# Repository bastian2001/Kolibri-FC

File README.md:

# RP2350 Flight Controller for FPV

I wanted to have some fun designing my own flight controller in both hardware and software. [This project of mine](https://github.com/bastian2001/Hardware-DShot-on-RP2040) ([superseded](https://github.com/bastian2001/pico-bidir-dshot/)) served as a proof of concept (and mostly minimal example) that the RP2040 is capable of driving DShot through the PIO (Programmable IO) hardware.

Main software features:

- Configurator
- Acro and angle modes
- altitude and position hold modes (working, but need to be tuned)
- ELRS
- GPS (UBlox) and Compass (HMC5883 + QMC5883L)
- Bidirectional DShot 4800 (tested up to 1200)
- Variable frequency beeper with WAV support
- SD-Blackbox incl. viewer
- Barometer (Goertek SPL06-001 + STM LPS22HB)

> [!NOTE]
> The PCB now lives in [its own repo](https://github.com/bastian2001/Kolibri-FC-Hardware)

Future shit:

- return to home and waypoint mission (incl. emergency switch)
- 3D camera dolly
- trick trainer, that does a trick for you and displays in the OSD how good or bad you were at repeating that trick

Practically speaking, is there any reason to choose this over Betaflight or iNav? Likely not, but I want to have a challenge.

## Configurator screenshots

Home Page with a general preview of the quad's orientation, some status info and general controls

The Hardware Setup Page allows you to tell the FC how you wired up everything, and how everything is attached together mechanically. You can create UARTs as much as the resources allow for it, normal or PIO based. It is all in one spot so you can quickly check whether all devices are recognized.

Blackbox viewer integrated into the configurator. You can record ELRS data, gyro rates, PID, a bunch of sensor data and much more. Size is practically unlimited (SD card logging), for me it is usually in the range of 80-150KB/s. Integrated filtering to smooth noisy data, multiple graphs and multiple traces per graph, JSON converter for external analysis, pinch to zoom (touchscreen support).

Tasks viewer shows the execution duration and frequency of all the tasks to check they're running fast enough and to aid optimization of code. Some functions are not always running, hence the NaN and 0Hz.

Receiver Page shows status of the RX and each channel. It also allows you to set which switch is used for arming etc., and you can set things up on the receiver, transmitter and other devices (ELRS 4.0+ required (maybe Crossfire also works)).

Tuning of PIDs and filters, as well as rates, with live preview of rates and Blender-style input boxes

GPS + Mag page shows X/Y Y/Z and Z/X graphs of the magnetometer to check calibration and skew. Lower side shows data obtained by the GPS (no GPS fix right now, so time is off)

CLI for some additional settings and easier development and testing of new ones

More features: Motor remapping and Analog VTX channel adjustment (IRC Tramp)

You can also connect via you ELRS' WiFi, and everything except very large CLI operations and the Tasks viewer works the same way (512 byte limit on ELRS side). Even blackbox data can be transmitted over WiFi.

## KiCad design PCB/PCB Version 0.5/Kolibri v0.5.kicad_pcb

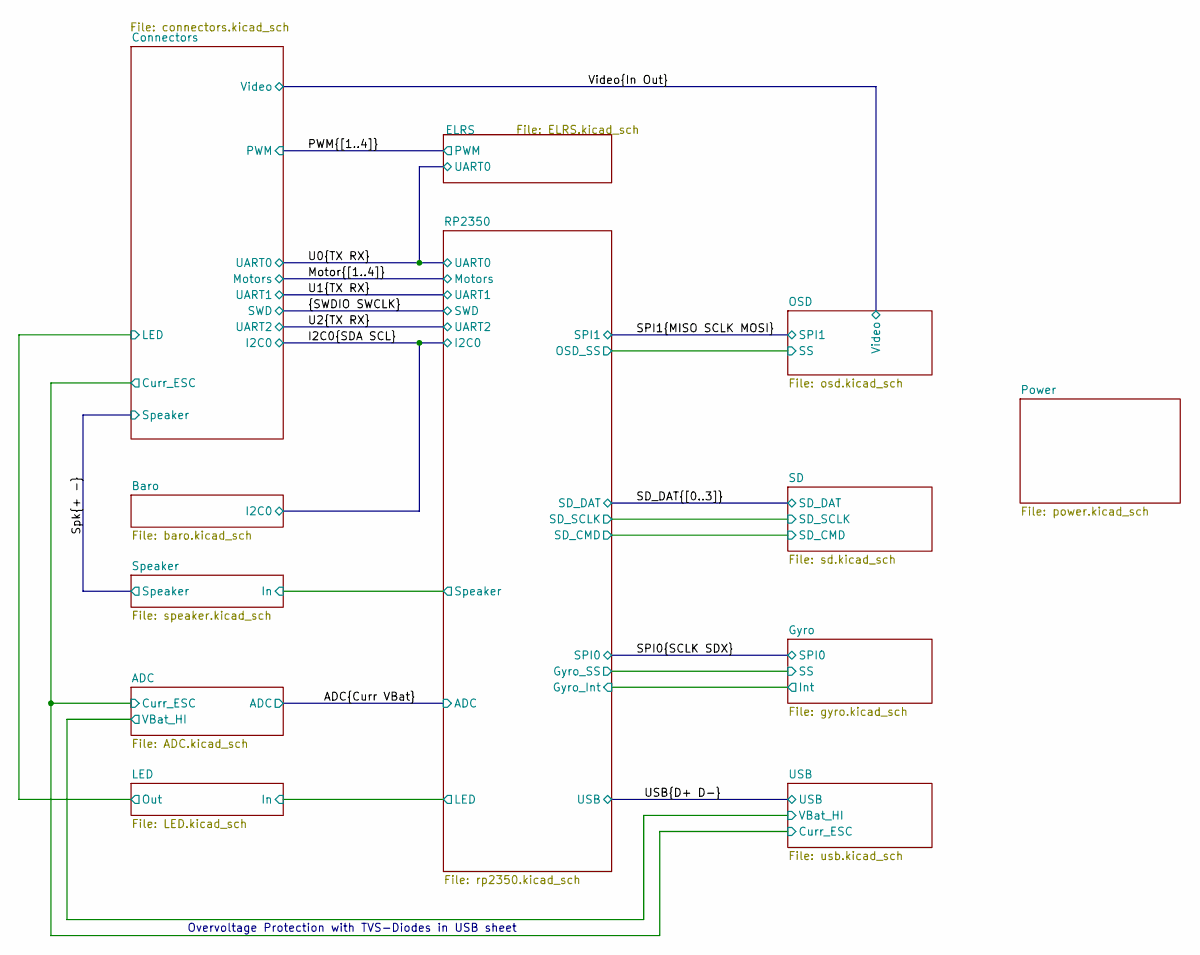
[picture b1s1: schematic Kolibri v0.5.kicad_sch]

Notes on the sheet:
Overvoltage Protection with TVS-Diodes in USB sheet

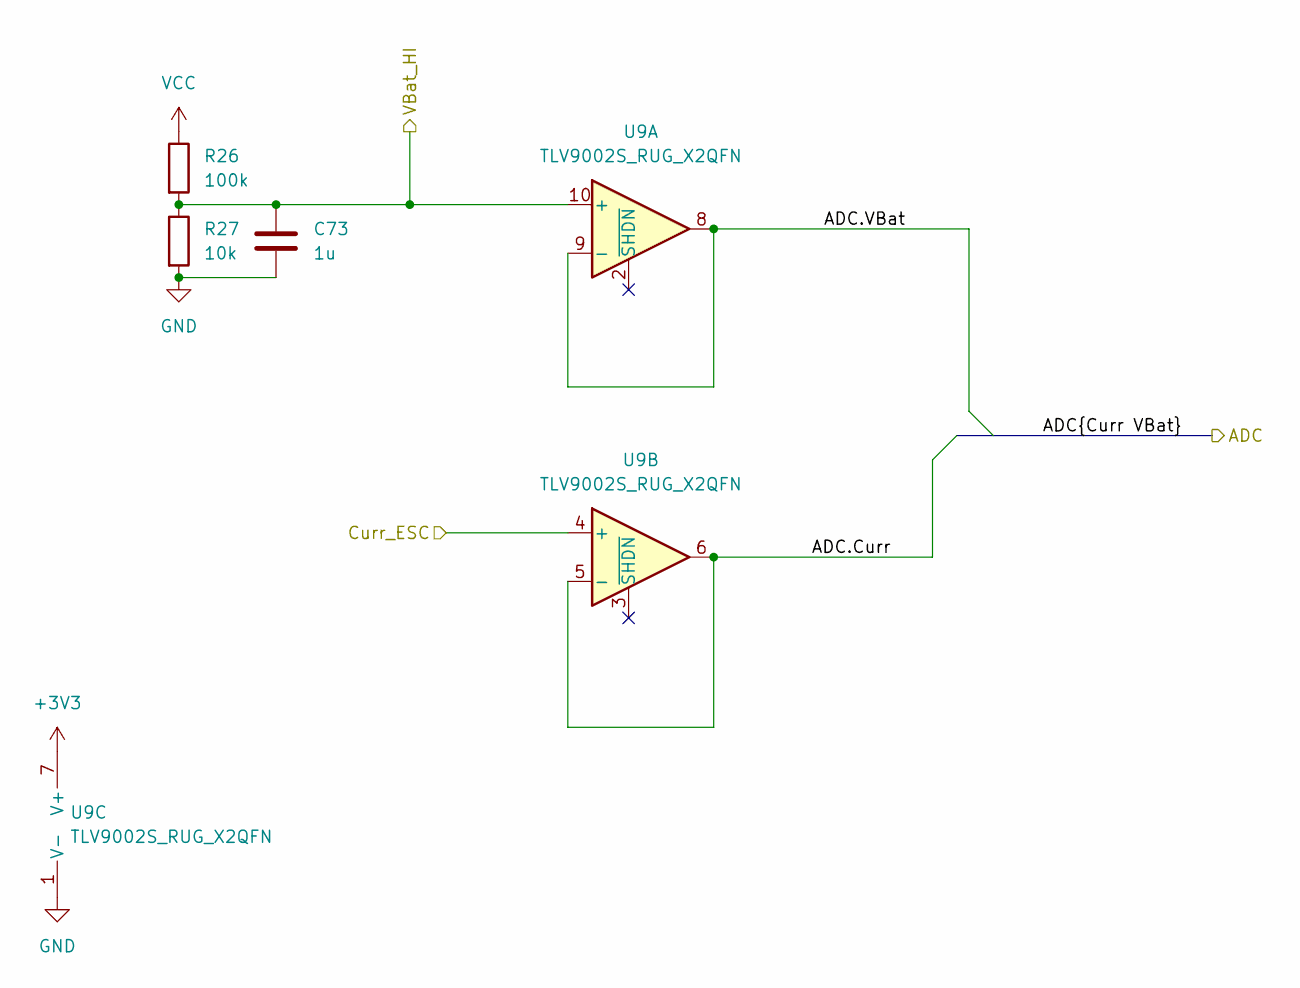
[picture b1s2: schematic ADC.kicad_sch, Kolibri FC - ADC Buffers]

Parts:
C73: 1u; C_0402_1005Metric
R26: 100k; R_0402_1005Metric
R27: 10k; R_0402_1005Metric
U9: TLV9002S_RUG_X2QFN; Texas_X2QFN_RUG_10pin_1.5x2mm

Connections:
+3V3: U9.7 (V+); also elsewhere on the board
/ADC.Curr: U9.5 (-), U9.6; also elsewhere on the board
/ADC.VBat: U9.8, U9.9 (-); also elsewhere on the board
/ADC/VBat_HI: C73.2, R26.2, R27.1, U9.10 (+); also elsewhere on the board
/Connectors/Curr_ESC: U9.4 (+); also elsewhere on the board
GND: C73.1, R27.2, U9.1 (V-); also elsewhere on the board

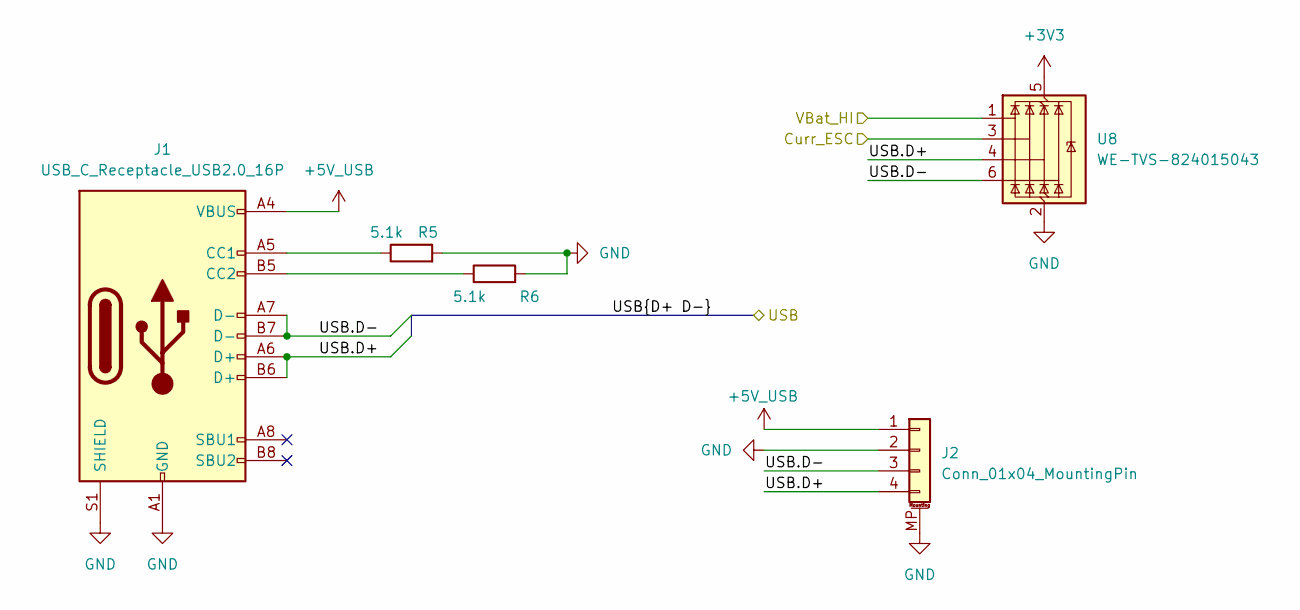
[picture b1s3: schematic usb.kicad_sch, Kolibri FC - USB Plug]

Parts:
J1: USB_C_Receptacle_USB2.0_16P; USB-C SMD+THT
J2: Conn_01x04_MountingPin; JST_SH_SM04B-SRSS-TB_1x04-1MP_P1.00mm_Horizontal
R5, R6: 5.1k; R_0402_1005Metric
U8: WE-TVS-824015043; SOT-23-6

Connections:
+3V3: U8.5 (VBUS); also elsewhere on the board
+5V_USB: J1.A4 (VBUS), J1.A9 (VBUS), J1.B4 (VBUS), J1.B9 (VBUS), J2.1; also elsewhere on the board
/ADC/VBat_HI: U8.1 (I/O1); also elsewhere on the board
/Connectors/Curr_ESC: U8.3 (I/O2); also elsewhere on the board
GND: J1.A1 (GND), J1.A12 (GND), J1.B1 (GND), J1.B12 (GND), J1.S1 (SHIELD), J2.2, J2.MP (MountPin), R5.2, R6.2, U8.2 (GND); also elsewhere on the board
unnamed: J1.A5 (CC1), R5.1
unnamed: J1.B5 (CC2), R6.1

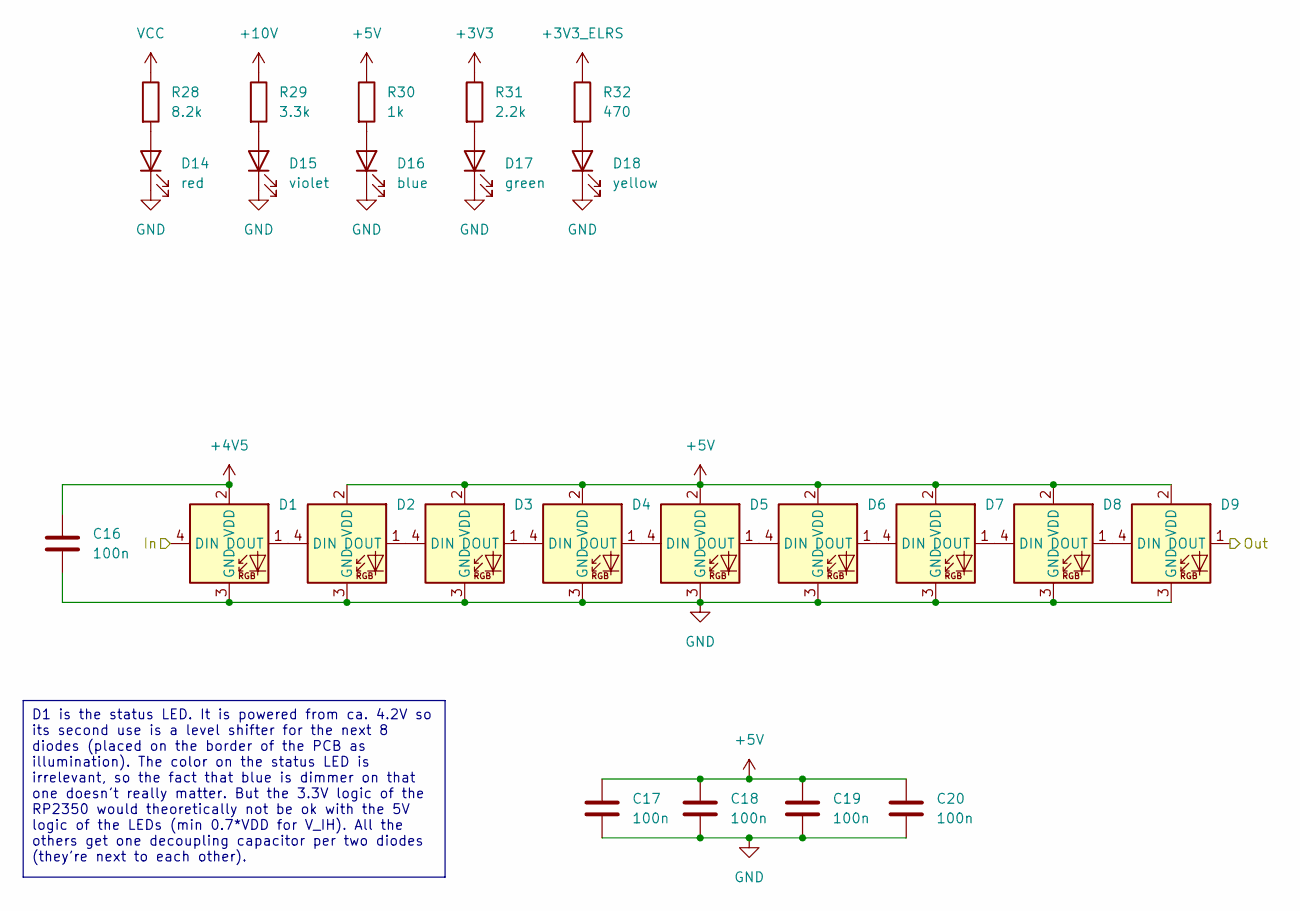
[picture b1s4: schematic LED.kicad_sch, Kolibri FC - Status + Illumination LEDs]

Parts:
C16, C17, C18, C19, C20: 100n; C_0402_1005Metric
D1, D2, D3, D4, D5, D6, D7, D8, D9: WS2812B_1615
D14: red; LED_0603_1608Metric
D15: violet; LED_0603_1608Metric
D16: blue; LED_0603_1608Metric
D17: green; LED_0603_1608Metric
D18: yellow; LED_0603_1608Metric
R28: 8.2k; R_0402_1005Metric_Pad0.72x0.64mm_HandSolder
R29: 3.3k; R_0402_1005Metric_Pad0.72x0.64mm_HandSolder
R30: 1k; R_0402_1005Metric_Pad0.72x0.64mm_HandSolder
R31: 2.2k; R_0402_1005Metric_Pad0.72x0.64mm_HandSolder
R32: 470; R_0402_1005Metric_Pad0.72x0.64mm_HandSolder

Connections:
+3V3: R31.1; also elsewhere on the board
+3V3_ELRS: R32.1; also elsewhere on the board
+4V5: C16.1, D1.2 (VDD); also elsewhere on the board
+5V: C17.1, C18.1, C19.1, C20.1, D2.2 (VDD), D3.2 (VDD), D4.2 (VDD), D5.2 (VDD), D6.2 (VDD), D7.2 (VDD), D8.2 (VDD), D9.2 (VDD), R30.1; also elsewhere on the board
/Connectors/LED: D9.1 (DOUT); also elsewhere on the board
/RP2350/LED: D1.4 (DIN); also elsewhere on the board
GND: C16.2, C17.2, C18.2, C19.2, C20.2, D1.3 (GND), D2.3 (GND), D3.3 (GND), D4.3 (GND), D5.3 (GND), D6.3 (GND), D7.3 (GND), D8.3 (GND), D9.3 (GND), D14.1 (K), D15.1 (K), D16.1 (K), D17.1 (K), D18.1 (K); also elsewhere on the board
unnamed: D1.1 (DOUT), D2.4 (DIN)
unnamed: D2.1 (DOUT), D3.4 (DIN)
unnamed: D3.1 (DOUT), D4.4 (DIN)
unnamed: D4.1 (DOUT), D5.4 (DIN)
unnamed: D5.1 (DOUT), D6.4 (DIN)
unnamed: D6.1 (DOUT), D7.4 (DIN)
unnamed: D7.1 (DOUT), D8.4 (DIN)
unnamed: D8.1 (DOUT), D9.4 (DIN)
unnamed: D14.2 (A), R28.2
unnamed: D15.2 (A), R29.2
unnamed: D16.2 (A), R30.2
unnamed: D17.2 (A), R31.2
unnamed: D18.2 (A), R32.2

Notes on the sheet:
D1 is the status LED. It is powered from ca. 4.2V so its second use is a level shifter for the next 8 diodes (placed on the border of the PCB as illumination). The color on the status LED is irrelevant, so the fact that blue is dimmer on that one doesn't really matter. But the 3.3V logic of the RP2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

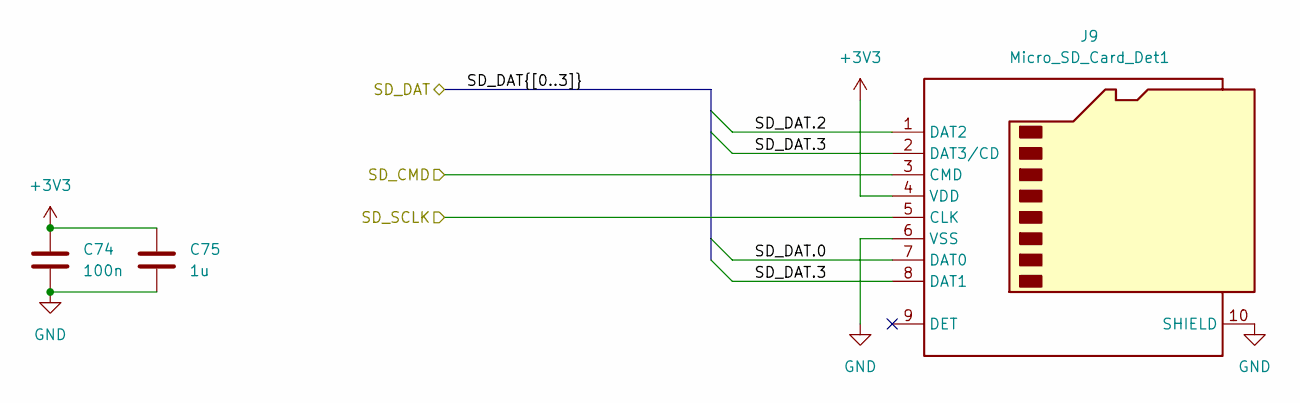
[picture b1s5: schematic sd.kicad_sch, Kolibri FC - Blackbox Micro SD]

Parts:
C74: 100n; C_0402_1005Metric_Pad0.74x0.62mm_HandSolder
C75: 1u; C_0402_1005Metric_Pad0.74x0.62mm_HandSolder
J9: Micro_SD_Card_Det1; Micro SD Card (TF)

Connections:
+3V3: C74.1, C75.1, J9.4 (VDD); also elsewhere on the board
/RP2350/SD_CMD: J9.3 (CMD); also elsewhere on the board
/RP2350/SD_SCLK: J9.5 (CLK); also elsewhere on the board
/SD_DAT.0: J9.7 (DAT0); also elsewhere on the board
/SD_DAT.2: J9.1 (DAT2); also elsewhere on the board
GND: C74.2, C75.2, J9.6 (VSS), J9.10 (SHIELD); also elsewhere on the board

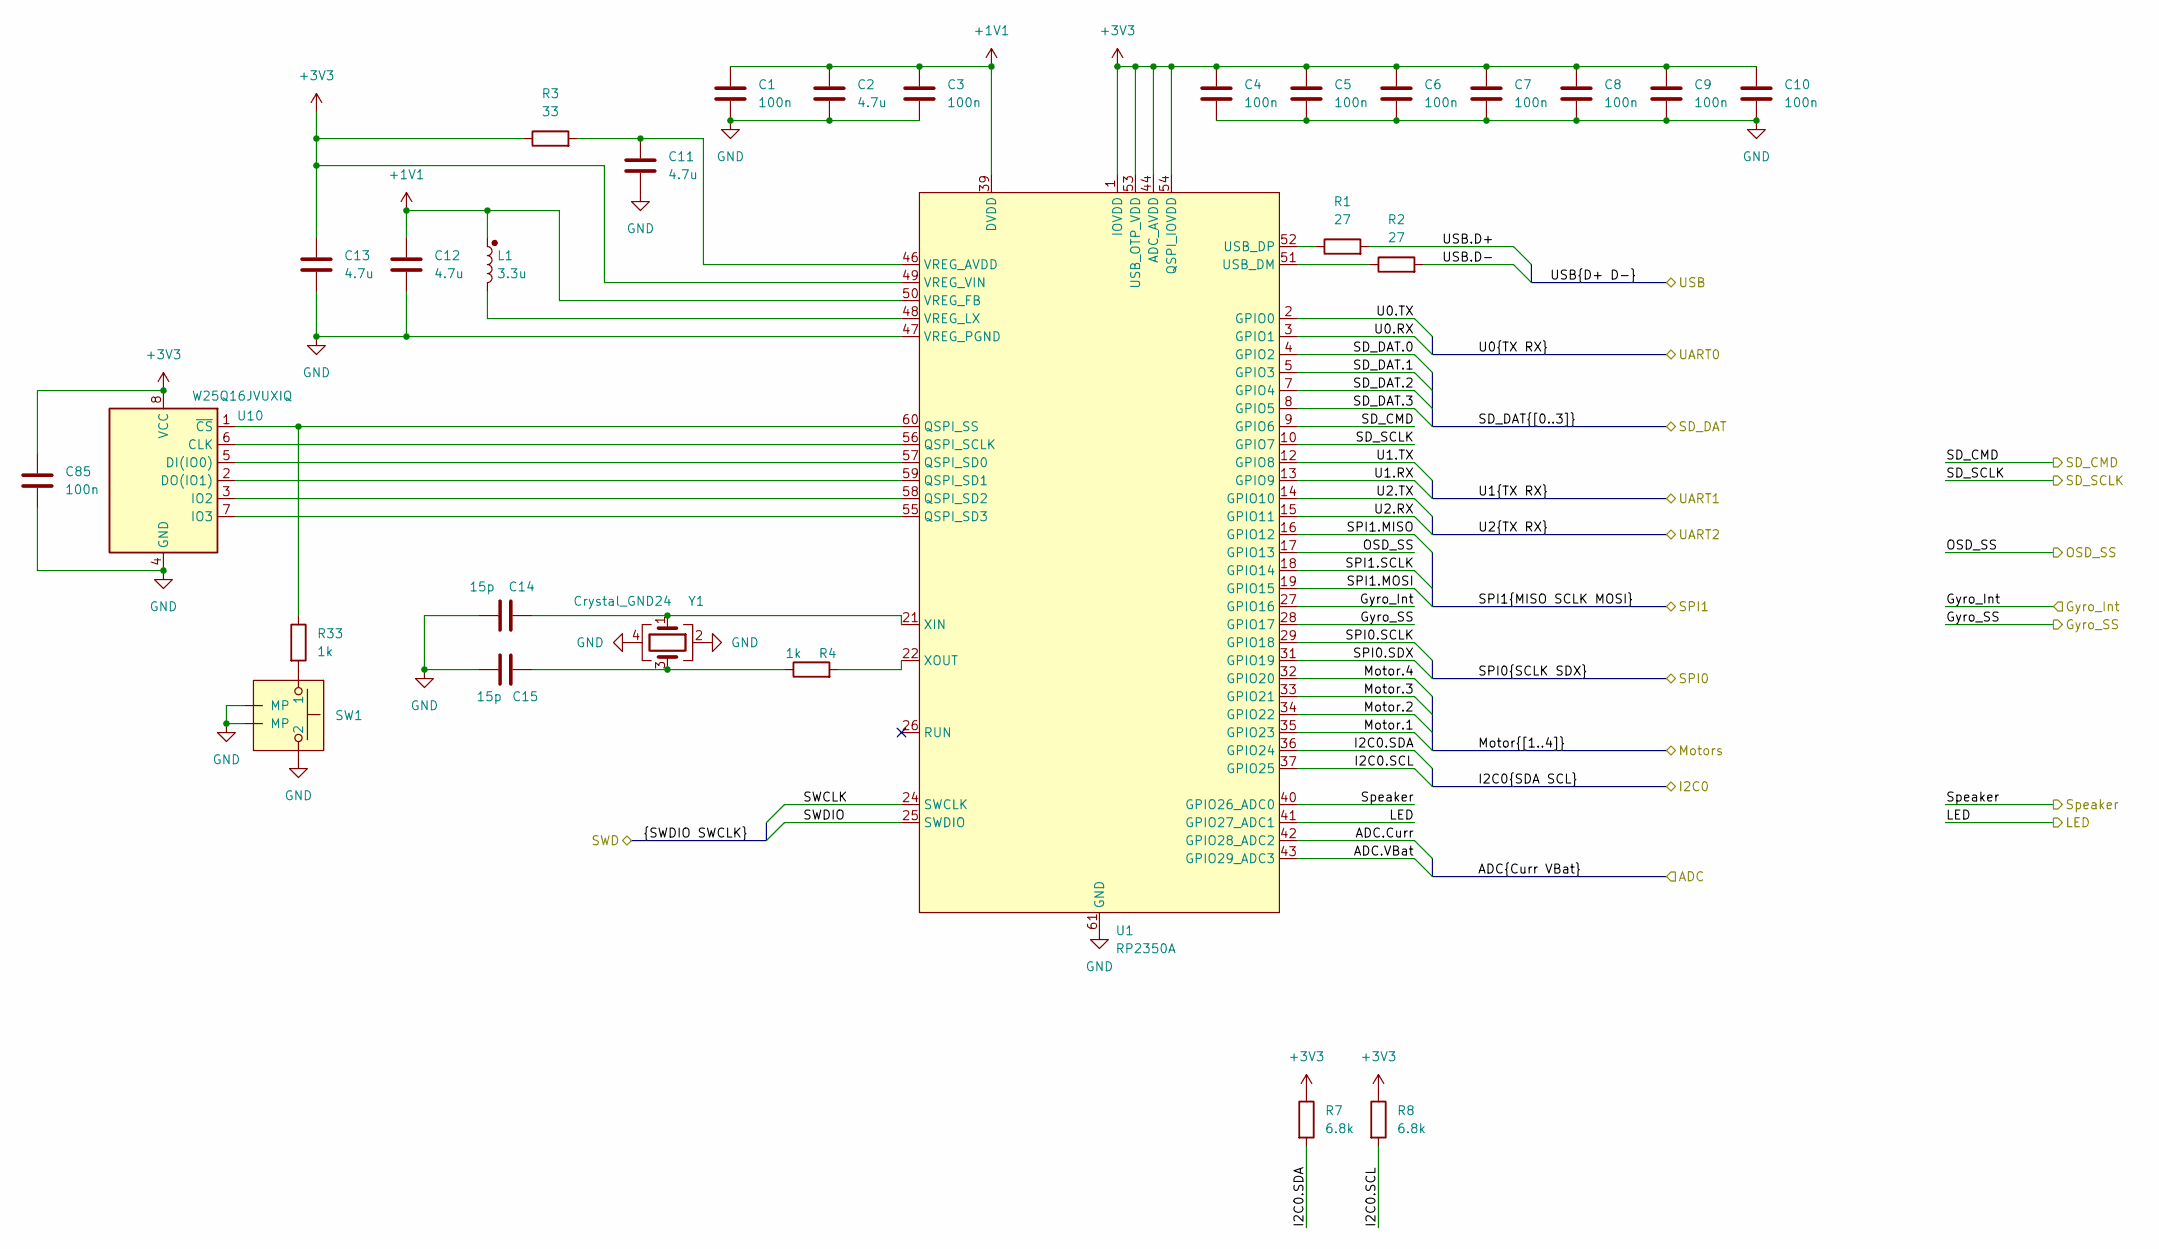
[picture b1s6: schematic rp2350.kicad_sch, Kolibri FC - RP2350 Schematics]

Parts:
C1, C3, C4, C5, C6, C7, C8, C9, C10: 100n; C_0402_1005Metric_Pad0.74x0.62mm_HandSolder
C2: 4.7u; C_0402_1005Metric_Pad0.74x0.62mm_HandSolder
C11, C12, C13: 4.7u; C_0402_1005Metric
C14, C15: 15p; C_0402_1005Metric_Pad0.74x0.62mm_HandSolder
C85: 100n; C_0402_1005Metric
L1: 3.3u; Abracon AOTA 0806
R1, R2: 27; R_0402_1005Metric
R3: 33; R_0402_1005Metric
R4, R33: 1k; R_0402_1005Metric_Pad0.72x0.64mm_HandSolder
R7, R8: 6.8k; R_0402_1005Metric_Pad0.72x0.64mm_HandSolder
SW1: Button C530669 wo holes
U1: RP2350A; QFN-60_EP_7x7_Pitch0.4mm
U10: W25Q16JVUXIQ; Winbond_USON-8-1EP_3x2mm_P0.5mm_EP0.2x1.6mm
Y1: Crystal_GND24; Crystal_SMD_3225-4Pin_3.2x2.5mm

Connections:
+1V1: C1.1, C2.1, C3.1, C12.1, L1.1, U1.6 (DVDD), U1.23 (DVDD), U1.39 (DVDD), U1.50 (VREG_FB)
+3V3: C4.1, C5.1, C6.1, C7.1, C8.1, C9.1, C10.1, C13.1, C85.1, R3.1, R7.1, R8.1, U1.1 (IOVDD), U1.11 (IOVDD), U1.20 (IOVDD), U1.30 (IOVDD), U1.38 (IOVDD), U1.44 (ADC_AVDD), U1.45 (IOVDD), U1.49 (VREG_VIN), U1.53 (USB_OTP_VDD), U1.54 (QSPI_IOVDD), U10.8 (VCC); also elsewhere on the board
/ADC.Curr: U1.42 (GPIO28_ADC2); also elsewhere on the board
/ADC.VBat: U1.43 (GPIO29_ADC3); also elsewhere on the board
/I2C0.SCL: R8.2, U1.37 (GPIO25); also elsewhere on the board
/I2C0.SDA: R7.2, U1.36 (GPIO24); also elsewhere on the board
/Motor.1: U1.35 (GPIO23); also elsewhere on the board
/Motor.2: U1.34 (GPIO22); also elsewhere on the board
/Motor.3: U1.33 (GPIO21); also elsewhere on the board
/Motor.4: U1.32 (GPIO20); also elsewhere on the board
/RP2350/Gyro_Int: U1.27 (GPIO16); also elsewhere on the board
/RP2350/Gyro_SS: U1.28 (GPIO17); also elsewhere on the board
/RP2350/LED: U1.41 (GPIO27_ADC1); also elsewhere on the board
/RP2350/OSD_SS: U1.17 (GPIO13); also elsewhere on the board
/RP2350/SD_CMD: U1.9 (GPIO6); also elsewhere on the board
/RP2350/SD_SCLK: U1.10 (GPIO7); also elsewhere on the board
/RP2350/Speaker: U1.40 (GPIO26_ADC0); also elsewhere on the board
/SD_DAT.0: U1.4 (GPIO2); also elsewhere on the board
/SD_DAT.2: U1.7 (GPIO4); also elsewhere on the board
/SPI0.SCLK: U1.29 (GPIO18); also elsewhere on the board
/SPI0.SDX: U1.31 (GPIO19); also elsewhere on the board
/SPI1.MISO: U1.16 (GPIO12); also elsewhere on the board
/SPI1.MOSI: U1.19 (GPIO15); also elsewhere on the board
/SPI1.SCLK: U1.18 (GPIO14); also elsewhere on the board
/SWCLK: U1.24 (SWCLK); also elsewhere on the board
/SWDIO: U1.25 (SWDIO); also elsewhere on the board
/U0.RX: U1.3 (GPIO1); also elsewhere on the board
/U0.TX: U1.2 (GPIO0); also elsewhere on the board
/U2.RX: U1.15 (GPIO11); also elsewhere on the board
/U2.TX: U1.14 (GPIO10); also elsewhere on the board
GND: C1.2, C2.2, C3.2, C4.2, C5.2, C6.2, C7.2, C8.2, C9.2, C10.2, C11.2, C12.2, C13.2, C14.1, C15.1, C85.2, SW1.2, SW1.3 (MP), SW1.4 (MP), U1.47 (VREG_PGND), U1.61 (GND), U10.4 (GND), U10.9 (EP), Y1.2, Y1.4; also elsewhere on the board
unnamed: C15.2, R4.1, Y1.3
unnamed: R33.2, SW1.1
unnamed: U1.56 (QSPI_SCLK), U10.6 (CLK)
unnamed: U1.57 (QSPI_SD0), U10.5 (DI(IO0))
unnamed: U1.59 (QSPI_SD1), U10.2 (DO(IO1))
unnamed: U1.58 (QSPI_SD2), U10.3 (IO2)
unnamed: U1.55 (QSPI_SD3), U10.7 (IO3)
unnamed: R33.1, U1.60 (QSPI_SS), U10.1 (~CS)
unnamed: R2.1, U1.51 (USB_DM)
unnamed: R1.1, U1.52 (USB_DP)
unnamed: C11.1, R3.2, U1.46 (VREG_AVDD)
unnamed: L1.2, U1.48 (VREG_LX)
unnamed: C14.2, U1.21 (XIN), Y1.1
unnamed: R4.2, U1.22 (XOUT)

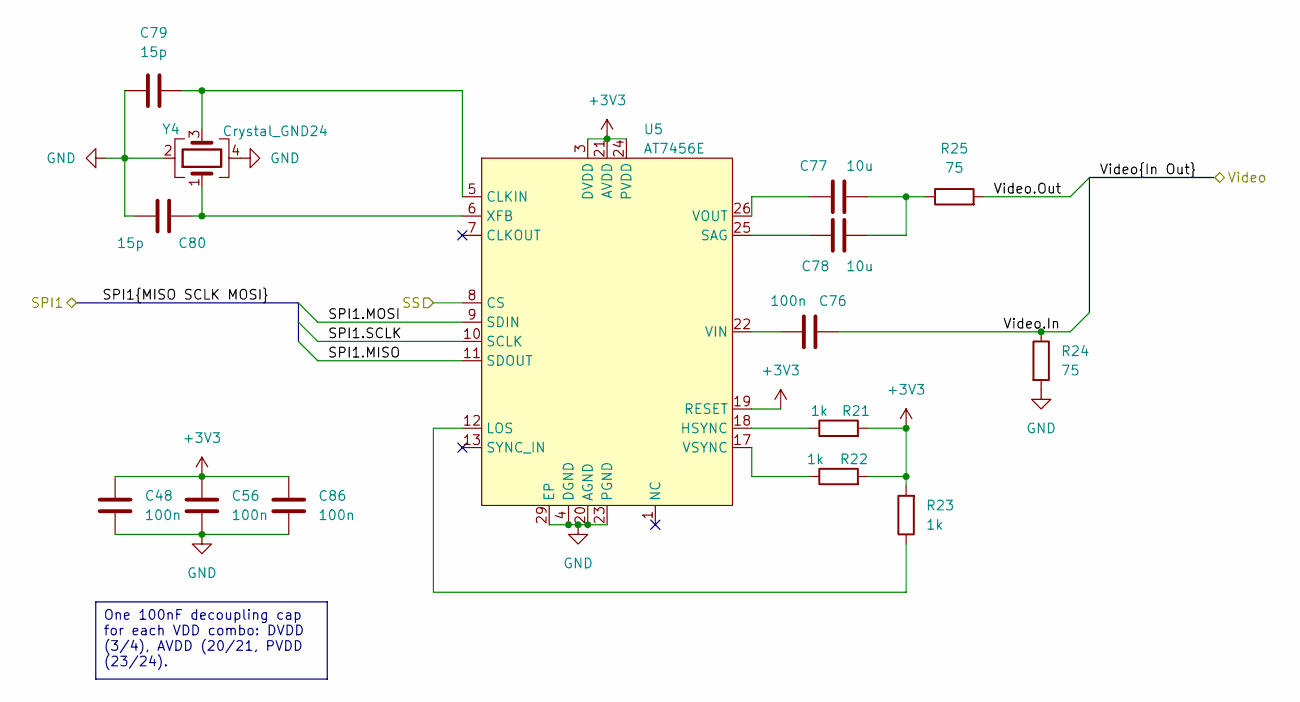
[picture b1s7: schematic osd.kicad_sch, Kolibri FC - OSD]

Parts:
C48, C76: 100n; C_0402_1005Metric
C56, C86: 100n; C_0402_1005Metric_Pad0.74x0.62mm_HandSolder
C77, C78: 10u; C_0402_1005Metric_Pad0.74x0.62mm_HandSolder
C79, C80: 15p; C_0402_1005Metric
R21, R22, R23: 1k; R_0402_1005Metric
R24: 75; R_0402_1005Metric
R25: 75; R_0402_1005Metric_Pad0.72x0.64mm_HandSolder
U5: AT7456E; HTSSOP-28-1EP_4.4x9.7mm_P0.65mm_EP2.75x6.2mm
Y4: Crystal_GND24; Crystal_SMD_3225-4Pin_3.2x2.5mm

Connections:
+3V3: C48.1, C56.1, C86.1, R21.2, R22.2, R23.2, U5.3 (DVDD), U5.19 (RESET), U5.21 (AVDD), U5.24 (PVDD); also elsewhere on the board
/RP2350/OSD_SS: U5.8 (CS); also elsewhere on the board
/SPI1.MISO: U5.11 (SDOUT); also elsewhere on the board
/SPI1.MOSI: U5.9 (SDIN); also elsewhere on the board
/SPI1.SCLK: U5.10 (SCLK); also elsewhere on the board
/Video.In: C76.2, R24.1; also elsewhere on the board
/Video.Out: R25.2; also elsewhere on the board
GND: C48.2, C56.2, C79.1, C80.2, C86.2, R24.2, U5.4 (DGND), U5.20 (AGND), U5.23 (PGND), U5.29 (EP), Y4.2, Y4.4; also elsewhere on the board
unnamed: C77.2, C78.1, R25.1
unnamed: C79.2, U5.5 (CLKIN), Y4.3
unnamed: R21.1, U5.18 (HSYNC)
unnamed: R23.1, U5.12 (LOS)
unnamed: C78.2, U5.25 (SAG)
unnamed: C76.1, U5.22 (VIN)
unnamed: R22.1, U5.17 (VSYNC)
unnamed: C80.1, U5.6 (XFB), Y4.1

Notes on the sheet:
One 100nF decoupling cap for each VDD combo: DVDD (3/4), AVDD (20/21, PVDD (23/24).

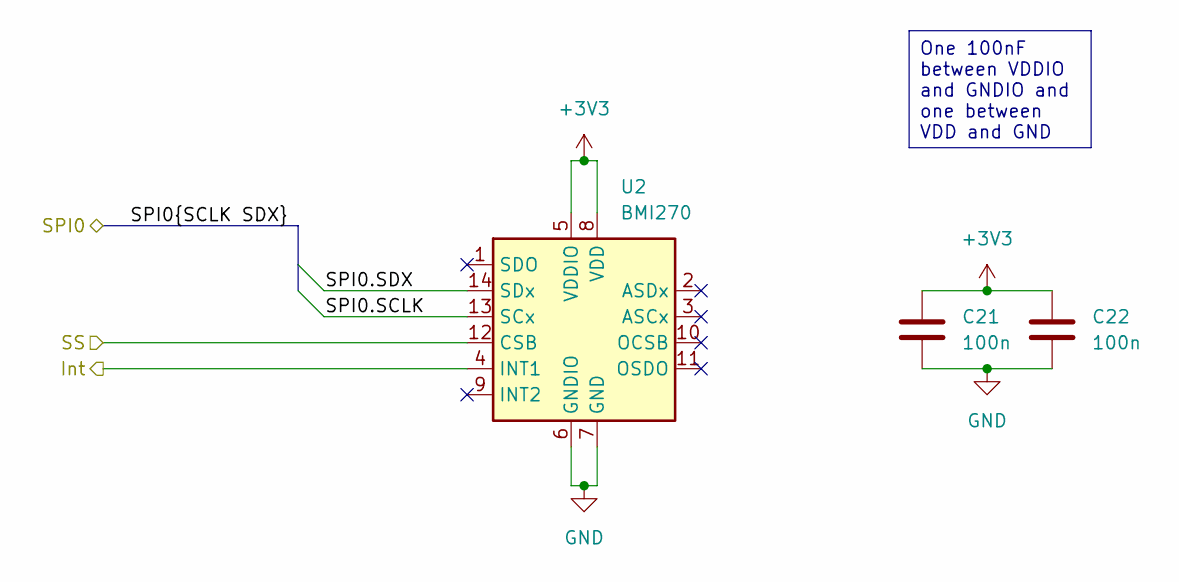
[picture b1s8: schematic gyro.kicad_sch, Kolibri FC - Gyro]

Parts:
C21, C22: 100n; C_0402_1005Metric
U2: BMI270; Bosch_LGA-14_3x2.5mm_P0.5mm

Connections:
+3V3: C21.1, C22.1, U2.5 (VDDIO), U2.8 (VDD); also elsewhere on the board
/RP2350/Gyro_Int: U2.4 (INT1); also elsewhere on the board
/RP2350/Gyro_SS: U2.12 (CSB); also elsewhere on the board
/SPI0.SCLK: U2.13 (SCx); also elsewhere on the board
/SPI0.SDX: U2.14 (SDx); also elsewhere on the board
GND: C21.2, C22.2, U2.6 (GNDIO), U2.7 (GND); also elsewhere on the board

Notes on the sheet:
One 100nF between VDDIO and GNDIO and one between VDD and GND

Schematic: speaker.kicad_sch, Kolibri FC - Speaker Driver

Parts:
D12: 1N4148WS; D_SOD-323
JP1: SolderJumper_3_Open; SolderJumper-3_P1.3mm_Open_RoundedPad1.0x1.5mm
Q1: BSS138; SOT-23

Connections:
/RP2350/Speaker: Q1.1 (G); also elsewhere on the board
/Spk.+: D12.1 (K), JP1.2 (C); also elsewhere on the board
/Spk.-: D12.2 (A), Q1.3 (D); also elsewhere on the board
GND: Q1.2 (S); also elsewhere on the board

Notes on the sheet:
PWM Speaker driver
Q1 acts as a pulldown, D12 is the flyback. Q1's gate is PWMed at 44.1kHz. By adjusting the duty cycle of the PWM, we can either pull Spk.- lower (higher duty cycle) or higher (lower duty cycle), to write our sound samples to Spk.-. This way, we get a DAC without proper DAC hardware. Alternatively, 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

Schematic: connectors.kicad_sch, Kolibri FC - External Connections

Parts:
J5: Conn_01x08_MountingPin; JST_SH_SM08B-SRSS-TB_1x08-1MP_P1.00mm_Horizontal
J6, J7: Conn_01x06_MountingPin; JST_SH_SM06B-SRSS-TB_1x06-1MP_P1.00mm_Horizontal
J8: Conn_01x03_MountingPin; JST_SH_SM03B-SRSS-TB_1x03-1MP_P1.00mm_Horizontal
P1, P2, P3, P4, P5, P6, P7, P8, P9, P10, P11, P12, P13, P14, P15, P16, P17: Solder_Pad_rounded
P18, P19, P20, P21, P22: Solder_Pad_rounded_dual
P23, P24, P25: Solder_Pad_rect_dual
P26, P27: Solder_Pad_rect
P28, P29, P30, P33, P34: Solder_Pad_octa_dual
P31, P32: Solder_Pad_octa

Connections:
+3V3: P34.1, P34.2; also elsewhere on the board
+5V: J6.4, P29.1, P29.2, P30.1, P30.2, P31.1, P32.1; also elsewhere on the board
/Connectors/Curr_ESC: J5.8, P5.1; also elsewhere on the board
/Connectors/LED: P20.1, P20.2; also elsewhere on the board
/I2C0.SCL: J6.6, P9.1; also elsewhere on the board
/I2C0.SDA: J6.5, P8.1; also elsewhere on the board
/Motor.1: J5.3, P1.1; also elsewhere on the board
/Motor.2: J5.4, P2.1; also elsewhere on the board
/Motor.3: J5.5, P3.1; also elsewhere on the board
/Motor.4: J5.6, P4.1; also elsewhere on the board
/PWM.1: P12.1; also elsewhere on the board
/PWM.2: P13.1; also elsewhere on the board
/PWM.3: P14.1; also elsewhere on the board
/PWM.4: P15.1; also elsewhere on the board
/SWCLK: J8.1; also elsewhere on the board
/SWDIO: J8.3; also elsewhere on the board
/Spk.+: P21.1, P21.2; also elsewhere on the board
/Spk.-: P22.1, P22.2; also elsewhere on the board
/U0.RX: P17.1; also elsewhere on the board
/U0.TX: P16.1; also elsewhere on the board
/U2.RX: J7.4, P11.1; also elsewhere on the board
/U2.TX: J7.3, P10.1; also elsewhere on the board
/Video.In: P18.1, P18.2; also elsewhere on the board
/Video.Out: P19.1, P19.2; also elsewhere on the board
GND: J5.1, J5.MP (MountPin), J6.3, J6.MP (MountPin), J7.2, J7.5, J7.MP (MountPin), J8.2, J8.MP (MountPin), P23.1, P23.2, P24.1, P24.2, P25.1, P25.2, P26.1, P27.1; also elsewhere on the board

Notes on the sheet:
Power, GND
GPS
LED, Speaker
SWD
Analog Video
ESC
uses Mamba pinout
ELRS PWM outputs
Digital VTX
ELRS UART

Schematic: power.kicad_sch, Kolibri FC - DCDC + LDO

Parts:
C63, C64: 1u; C_0603_1608Metric
C65, C71: 100n; C_0402_1005Metric
C66: 47u; C_1206_3216Metric
C67, C70: 100n; C_0402_1005Metric_Pad0.74x0.62mm_HandSolder
C68, C69: 2.2u; C_1206_3216Metric
C72: 22u; C_0805_2012Metric
C81, C82, C83, C84: 1u; C_0402_1005Metric
D10, D13: 1N4148WS; D_SOD-323
IC5, IC6: LMR38025SDRRR; SON50P300X300X80-13N; Mouser Part Number 595-LMR38025SDRRR
L7, L8: 4.7u; L_Cenker_CKCS4020
R13: 100k; R_0402_1005Metric
R14: 39k; R_0402_1005Metric
R15: 40.2k; R_0402_1005Metric_Pad0.72x0.64mm_HandSolder
R16, R20: 10k; R_0402_1005Metric_Pad0.72x0.64mm_HandSolder
R17: 22.6k; R_0402_1005Metric
R18: 21.5k; R_0402_1005Metric
R19: 90.9k; R_0402_1005Metric_Pad0.72x0.64mm_HandSolder
U4: TPS2116DRL; SOT-583-8
U6: LP5912-3.3DRV; WSON-6-1EP_2x2mm_P0.65mm_EP1x1.6mm_ThermalVias
U7: TPS746-3.3DRV; WSON-6-1EP_2x2mm_P0.65mm_EP1x1.6mm_ThermalVias

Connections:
+3V3: C82.1, U6.1 (OUT); also elsewhere on the board
+3V3_ELRS: C84.1, U7.1 (OUT); also elsewhere on the board
+4V5: D10.1 (K); also elsewhere on the board
+5V: C63.2, C64.2, C81.1, C83.1, D10.2 (A), D13.1 (K), U4.2 (VOUT), U4.7 (VOUT), U6.4 (EN), U6.6 (IN), U7.4 (EN), U7.6 (IN); also elsewhere on the board
+5V_BUCK: C66.1, D13.2 (A), L7.2, R13.1, R15.1, U4.3 (VIN1), U4.5 (MODE)
+5V_USB: U4.6 (VIN2); also elsewhere on the board
GND: C63.1, C64.1, C66.2, C67.2, C68.2, C69.2, C70.2, C72.2, C81.2, C82.2, C83.2, C84.2, IC5.1 (GND_1), IC5.2 (GND_2), IC5.13 (EPAD), IC6.1 (GND_1), IC6.2 (GND_2), IC6.13 (EPAD), R14.2, R16.2, R17.2, R18.2, R20.2, U4.1 (GND), U6.3 (PG), U6.5 (GND), U6.7 (EP), U7.3 (GND), U7.5 (PG), U7.7 (EP); also elsewhere on the board
unnamed: C65.1, IC5.10 (BOOT)
unnamed: IC5.8 (FB), R15.2, R16.1
unnamed: IC5.7 (RT/SYNC), R17.1
unnamed: C65.2, IC5.11 (SW_1), IC5.12 (SW_2), L7.1
unnamed: C71.1, IC6.10 (BOOT)
unnamed: IC6.8 (FB), R19.2, R20.1
unnamed: IC6.7 (RT/SYNC), R18.1
unnamed: C71.2, IC6.11 (SW_1), IC6.12 (SW_2), L8.1
unnamed: R13.2, R14.1, U4.4 (PR1)

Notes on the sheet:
Two separate 3.3V-rails to satisfy ELRS's requirement of a separate 3.3V supply. Both LDOs have an almost identical pinout where only PG and GND are swapped, but because both allow PG to be grounded, these can be used interchangeably, once testing is complete (if ELRS is ok with only 500mA).
Switches up to 4A (TPS2117) from +5V_USB or +5V_BUCK to +5V. Prefers buck over USB, threshold voltage is about 3.5V. The threshold voltage is low to prevent accidental switchover to USB during peak consumption (worst case in flight). Emergency diode for if that happens during flight.
12-45V -> 10V 2.5A (6.8uH inductor recommended, but this works)
3.3V 1A LDO (ELRS)
Used for the first RGB LED in each strip, not broken out.
12-45V -> 5V 2.5A
3.3V 500mA LDO (main)
4.2V Supply
5V SMPS
5V Power MUX
10V SMPS

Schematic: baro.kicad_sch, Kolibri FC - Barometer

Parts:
C23, C24: 100n; C_0402_1005Metric_Pad0.74x0.62mm_HandSolder
U11: LPS22HB; ST_HLGA-10_2x2mm_P0.5mm_LayoutBorder3x2y

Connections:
+3V3: C23.1, C24.1, U11.1 (Vdd_IO), U11.5 (SA0), U11.6 (~CS), U11.10 (VDD); also elsewhere on the board
/I2C0.SCL: U11.2 (SCL); also elsewhere on the board
/I2C0.SDA: U11.4 (SDA); also elsewhere on the board
GND: C23.2, C24.2, U11.3 (GND), U11.8 (GND), U11.9 (GND); also elsewhere on the board

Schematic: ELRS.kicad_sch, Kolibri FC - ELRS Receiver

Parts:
C25, C26, C27, C28, C33, C34, C40, C44, C45, C60, C62: 100n; C_0402_1005Metric_Pad0.74x0.62mm_HandSolder
C29, C30, C35, C50, C53: 1u; C_0402_1005Metric_Pad0.74x0.62mm_HandSolder
C31, C42, C43, C47, C55: 10n; C_0402_1005Metric_Pad0.74x0.62mm_HandSolder
C32: 1.5p; C_0402_1005Metric
C36: 10u; C_0402_1005Metric_Pad0.74x0.62mm_HandSolder
C37: 1.5p; C_0402_1005Metric_Pad0.74x0.62mm_HandSolder
C38, C39: 15p; C_0402_1005Metric_Pad0.74x0.62mm_HandSolder
C41, C61: 470n; C_0402_1005Metric_Pad0.74x0.62mm_HandSolder
C46, C57: 47p; C_0402_1005Metric
C49: 220p; C_0402_1005Metric_Pad0.74x0.62mm_HandSolder
C51, C52, C58, C59: DNF; C_0402_1005Metric
C54: 220p; C_0402_1005Metric
D11: WS2812B_1615
FL1, FL2: 2450FM07D0034T; Mouser Part Number 609-2450FM07D0034T
IC1, IC3: SX1280IMLTRT; QFN50P400X400X100-25N-D; Mouser Part Number 947-SX1280IMLTRT
IC2, IC4: RFX2401C; QFN50P300X300X60-17N-D; Mouser Part Number 477-RFX2401C
J3, J4: Conn_Coaxial_Small; U.FL_Molex_MCRF_73412-0110_Vertical
L2: 2.0n; L_0402_1005Metric_Pad0.77x0.64mm_HandSolder
L3: 3.0n; L_0402_1005Metric
L4: 24n; L_0402_1005Metric
L5, L6: 15u; L_0805_2012Metric
R9, R10, R11, R12: 100k; R_0402_1005Metric_Pad0.72x0.64mm_HandSolder
SW2: Button C530669 wo holes
U3: ESP32-U4WDH; QFN-48_EP_5x5_Pitch0.35mm
Y2, Y3, Y5: Crystal_GND24; Crystal_SMD_2016-4Pin_2.0x1.6mm

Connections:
+3V3_ELRS: C25.1, C26.1, C27.1, C28.1, C29.1, C30.1, C34.1, C35.1, C36.1, C44.1, C45.1, C49.1, C50.1, C53.1, C54.1, C60.1, C62.1, IC1.11 (VBAT_IO), IC1.15 (VBAT), IC2.16 (VDD_2), IC3.11 (VBAT_IO), IC3.15 (VBAT), IC4.16 (VDD_2), L2.1, R9.1, R11.1, U3.1 (VDDA), U3.9 (CHIP_PU), U3.19 (VDD3P3_RTC), U3.26 (VDD_SDIO), U3.37 (VDD3P3_CPU), U3.43 (VDDA), U3.46 (VDDA); also elsewhere on the board
+4V5: C40.1, D11.2 (VDD); also elsewhere on the board
/ELRS/ELRS_BUTTON: SW2.2, U3.23 (GPIO0/S1)
/ELRS/LED_RGB: D11.4 (DIN), U3.21 (GPIO15/S1)
/ELRS/POWER_RXEN: IC2.6 (RXEN), R9.2, U3.20 (GPIO13)
/ELRS/POWER_RXEN2: U3.34 (GPIO5/S1)
/ELRS/POWER_RXEN_2: IC4.6 (RXEN), R11.2
/ELRS/POWER_TXEN: IC2.5 (TXEN), R10.1, U3.17 (GPIO14)
/ELRS/POWER_TXEN_2: IC4.5 (TXEN), R12.1, U3.35 (GPIO18)
/ELRS/RADIO_BUSY: IC1.7 (BUSY), U3.5 (GPI36)
/ELRS/RADIO_BUSY_2: IC3.7 (BUSY), U3.8 (GPI39)
/ELRS/RADIO_DIO1: IC1.8 (DIO1), U3.6 (GPI37)
/ELRS/RADIO_DIO1_2: IC3.8 (DIO1), U3.10 (GPI34)
/ELRS/RADIO_MISO: IC1.16 (MISO_TX), IC3.16 (MISO_TX), U3.11 (GPI35)
/ELRS/RADIO_MOSI: IC1.17 (MOSI_RX), IC3.17 (MOSI_RX), U3.12 (GPIO32)
/ELRS/RADIO_NSS: IC1.19 (NSS_CTS), U3.16 (GPIO27)
/ELRS/RADIO_NSS_2: IC3.19 (NSS_CTS), U3.38 (GPIO19)
/ELRS/RADIO_RST: IC1.3 (NRESET), U3.15 (GPIO26)
/ELRS/RADIO_RST_2: IC3.3 (NRESET), U3.42 (GPIO21)
/ELRS/RADIO_SCK: IC1.18 (SCK_RTSN), IC3.18 (SCK_RTSN), U3.13 (GPIO33)
/ELRS/WIFI_ANTENNA: C37.1, L3.1
/PWM.1: U3.24 (GPIO4); also elsewhere on the board
/PWM.2: U3.39 (GPIO22); also elsewhere on the board
/PWM.3: U3.36 (GPIO23); also elsewhere on the board
/PWM.4: U3.14 (GPIO25); also elsewhere on the board
/U0.RX: U3.41 (GPIO1/U0TX); also elsewhere on the board
/U0.TX: U3.40 (GPIO3/U0RX); also elsewhere on the board
GND: C25.2, C26.2, C27.2, C28.2, C29.2, C30.2, C31.1, C32.2, C33.2, C34.2, C35.2, C36.2, C37.2, C38.1, C39.1, C40.2, C41.1, C42.1, C43.2, C44.2, C45.2, C47.1, C49.2, C50.2, C51.1, C52.1, C53.2, C54.2, C55.2, C58.1, C59.1, C60.2, C61.1, C62.2, D11.3 (GND), FL1.2 (GND_1), FL1.4 (GND_2), FL2.2 (GND_1), FL2.4 (GND_2), IC1.5 (GND_1), IC1.13 (GND_2), IC1.20 (GND_3), IC1.21 (GND_4), IC1.23 (GND_5), IC1.24 (GND_6), IC1.25 (EP), IC2.1 (N/C_1), IC2.2 (GND_1), IC2.3 (GND_2), IC2.7 (N/C_2), IC2.8 (GND_3), IC2.9 (GND_4), IC2.11 (GND_5), IC2.12 (N/C_3), IC2.15 (N/C_4), IC2.17 (GND_6), IC3.5 (GND_1), IC3.13 (GND_2), IC3.20 (GND_3), IC3.21 (GND_4), IC3.23 (GND_5), IC3.24 (GND_6), IC3.25 (EP), IC4.1 (N/C_1), IC4.2 (GND_1), IC4.3 (GND_2), IC4.7 (N/C_2), IC4.8 (GND_3), IC4.9 (GND_4), IC4.11 (GND_5), IC4.12 (N/C_3), IC4.15 (N/C_4), IC4.17 (GND_6), J3.2 (Ext), J4.2 (Ext), R10.2, R12.2, SW2.1, SW2.3 (MP), SW2.4 (MP), U3.49 (GND), Y2.2, Y2.4, Y3.2, Y3.4, Y5.2, Y5.4; also elsewhere on the board
unnamed: C39.2, L4.1, Y2.1
unnamed: FL1.1 (IN), IC1.22 (RFIO)
unnamed: FL1.3 (OUT), IC2.4 (TXRX)
unnamed: FL2.1 (IN), IC3.22 (RFIO)
unnamed: FL2.3 (OUT), IC4.4 (TXRX)
unnamed: C41.2, C42.2, IC1.2 (VDD_IN), IC1.12 (DCC_FB), L5.1
unnamed: IC1.14 (DCC_SW), L5.2
unnamed: C43.1, IC1.1 (VR_PA)
unnamed: IC1.4 (XTA), Y5.3
unnamed: IC1.6 (XTB), Y5.1
unnamed: C46.2, C52.2, IC2.10 (ANT)
unnamed: C47.2, C61.2, IC3.2 (VDD_IN), IC3.12 (DCC_FB), L6.1
unnamed: IC3.14 (DCC_SW), L6.2
unnamed: C55.1, IC3.1 (VR_PA)
unnamed: IC3.4 (XTA), Y3.3
unnamed: IC3.6 (XTB), Y3.1
unnamed: C57.2, C59.2, IC4.10 (ANT)
unnamed: C46.1, C51.2, J3.1 (In)
unnamed: C57.1, C58.2, J4.1 (In)
unnamed: C31.2, U3.48 (CAP1)
unnamed: C32.1, L3.2, U3.2 (LNA_IN)
unnamed: C38.2, U3.44 (XTAL_N), Y2.3
unnamed: L4.2, U3.45 (XTAL_P)
VDD3P3: C33.1, L2.2, U3.3 (VDD3P3), U3.4 (VDD3P3)

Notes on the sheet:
C37635335
MTDI = 12, MTDO = 15
C46, C51, C52, C57, C58, C59 can either be fitted with only a coupling capacitor (C46, C57) or a pi filter, where C46 and C57 are inductors (~2.4nH, the other caps are ~1.2pF).
9pF load capacitance, C38 + C39 = 7.5pF, and some stray capacitance
On AT2401C, all N/C pads shall be connected to GND. Pin 13 is still DNC. Pin 14 VDD_1 is disconnected in both RFX2401C and AT2401C reference schematics.
1u caps for VDD_SDIO and VDDA (pin 43 or 46), 100n for all other pins

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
